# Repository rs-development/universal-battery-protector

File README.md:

# Work in Progress

# Universal Battery Protector
A Universal Battery Protector for Lithium Batteries with 2 to 6 Cells in series.

# LICENSE
<br />This work is licensed under a <a rel="license" href="http://creativecommons.org/licenses/by-sa/3.0/">Creative Commons Attribution-ShareAlike 3.0 Unported License</a>.

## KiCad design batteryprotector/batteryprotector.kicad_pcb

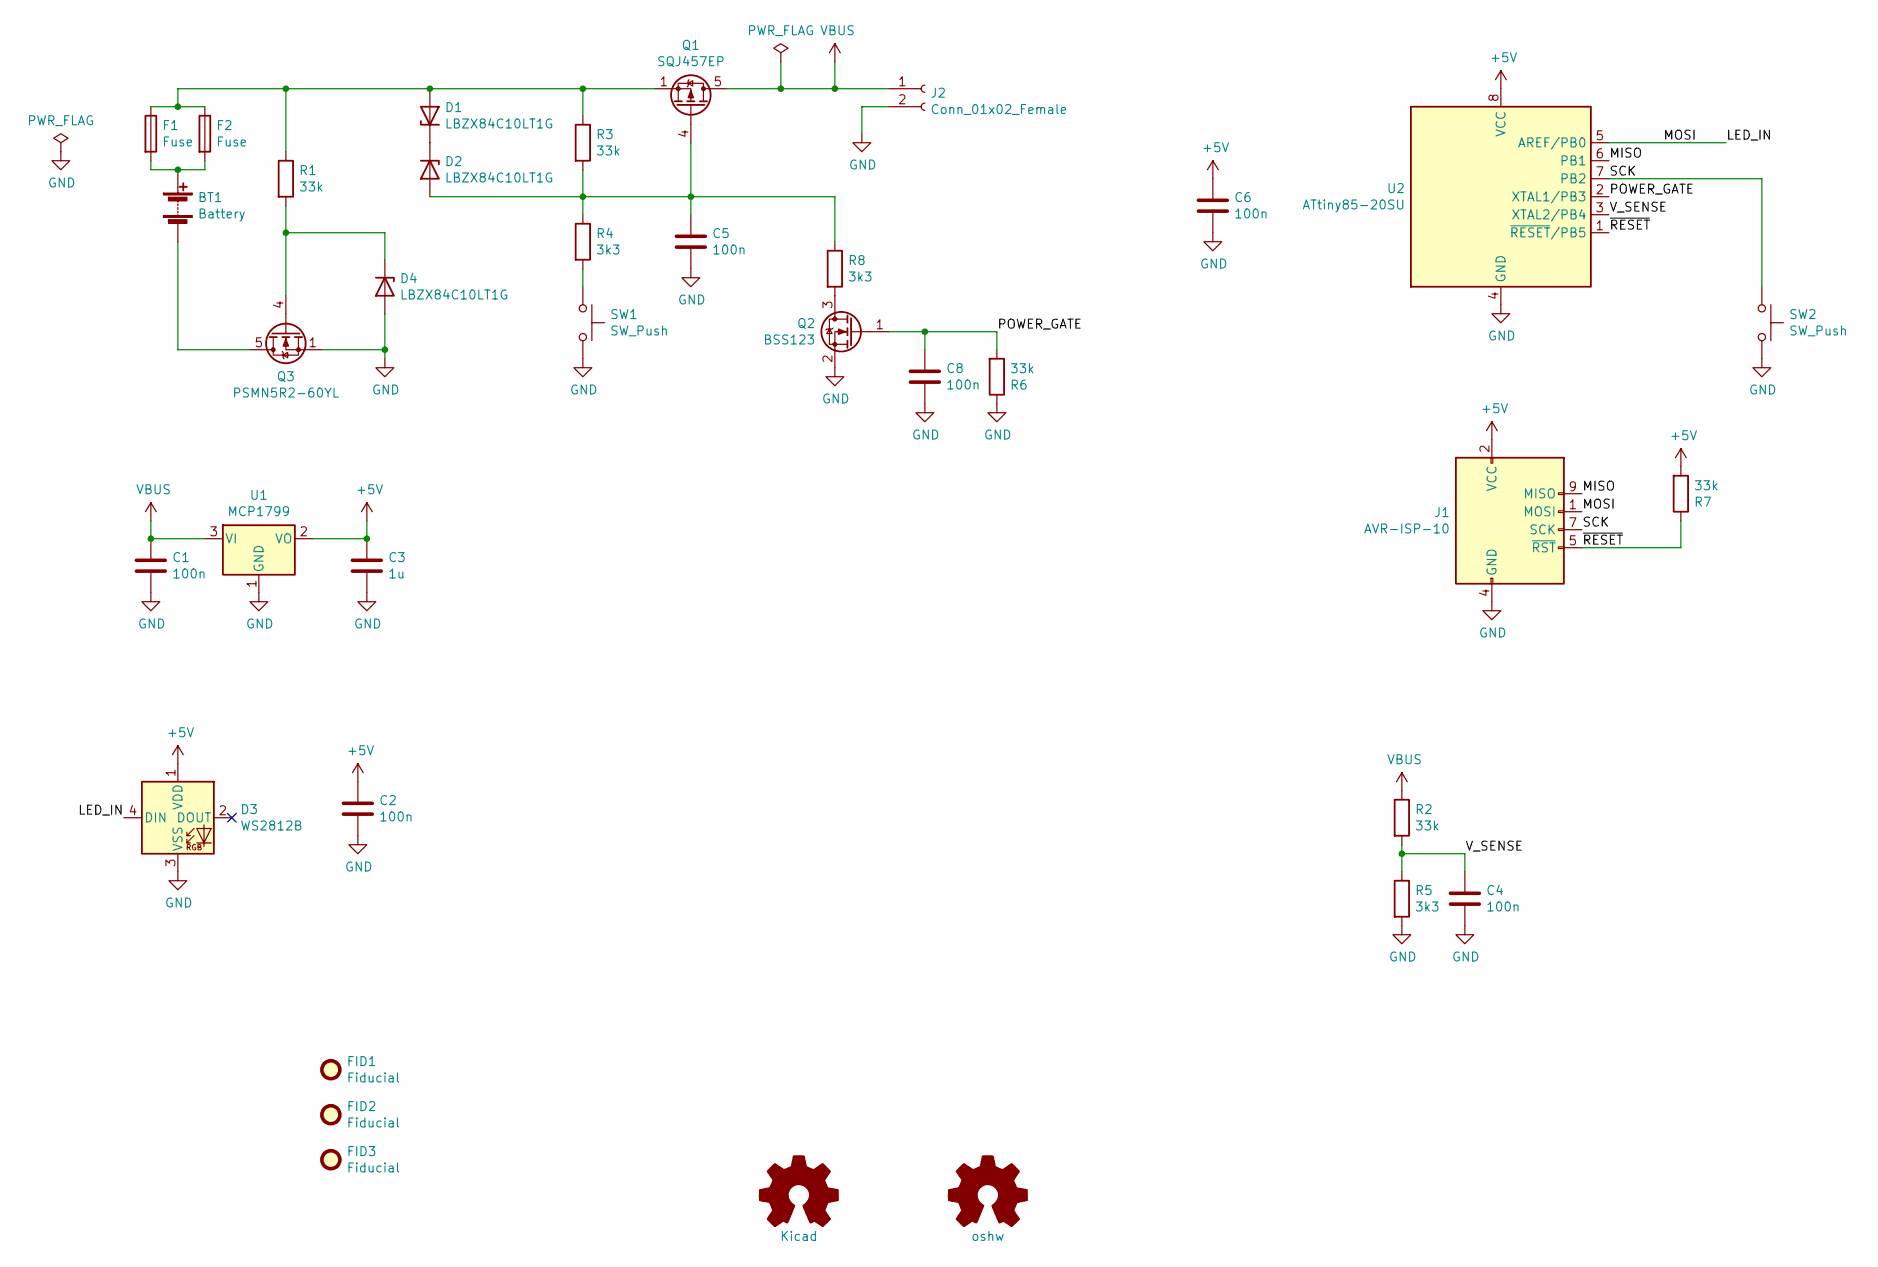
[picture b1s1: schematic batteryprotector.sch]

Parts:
BT1: Battery; AMASS_XT60-M_1x02_P7.20mm_Horizontal
C1, C2, C4, C5, C6, C8: 100n; C_0805_2012Metric
C3: 1u; C_0805_2012Metric
D1, D2, D4: LBZX84C10LT1G; D_SOT-23_ANK
D3: WS2812B; LED_WS2812B_PLCC4_5.0x5.0mm_P3.2mm
F1: Fuse; Fuse_1206_3216Metric
F2: Fuse; Fuse_0603_1608Metric
FID1, FID2, FID3: Fiducial; Fiducial_1mm_Mask2mm_Paste
J1: AVR-ISP-10; Tag-Connect_TC2050-IDC-NL_2x05_P1.27mm_Vertical
J2: Conn_01x02_Female; AMASS_XT60-F_1x02_P7.20mm_Horizontal
LOGO1: oshw; OSHW-Logo2_7.3x6mm_SilkScreen
LOGO2: Kicad; KiCad-Logo2_5mm_SilkScreen
Q1: SQJ457EP; LFPAK56
Q2: BSS123; SOT-23
Q3: PSMN5R2-60YL; LFPAK56
R1, R2, R3, R6, R7: 33k; R_0805_2012Metric
R4, R5, R8: 3k3; R_0805_2012Metric
SW1, SW2: SW_Push; SW_SPST_PTS810
U1: MCP1799; SOT-23
U2: ATtiny85-20SU; SOIJ-8_5.3x5.3mm_P1.27mm

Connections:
+5V: C2.1, C3.1, C6.1, D3.1 (VDD), J1.2 (VCC), R7.2, U1.2 (VO), U2.8 (VCC)
/LED_IN: D3.4 (DIN), J1.1 (MOSI), U2.5 (AREF/PB0)
/MISO: J1.9 (MISO), U2.6 (PB1)
/POWER_GATE: C8.1, Q2.1 (G), R6.2, U2.2 (XTAL1/PB3)
/SCK: J1.7 (SCK), SW2.1, U2.7 (PB2)
/V_SENSE: C4.1, R2.2, R5.1, U2.3 (XTAL2/PB4)
/~RESET: J1.5 (~RST), R7.1, U2.1 (~RESET~/PB5)
GND: C1.2, C2.2, C3.2, C4.2, C5.2, C6.2, C8.2, D3.3 (VSS), D4.2 (A), J1.4 (GND), J1.6 (GND), J1.8 (GND), J1.10 (GND), J2.2, Q2.2 (S), Q3.1 (S), Q3.2 (S), Q3.3 (S), R5.2, R6.1, SW1.2, SW2.2, U1.1 (GND), U2.4 (GND)
unnamed: BT1.1 (+), F1.2, F2.2
unnamed: BT1.2 (-), Q3.5 (D)
unnamed: C5.1, D2.2 (A), Q1.4 (G), R3.2, R4.1, R8.1
unnamed: D1.1 (K), D2.1 (K)
unnamed: D1.2 (A), F1.1, F2.1, Q1.1 (S), Q1.2 (S), Q1.3 (S), R1.1, R3.1
unnamed: D4.1 (K), Q3.4 (G), R1.2
unnamed: Q2.3 (D), R8.2
unnamed: R4.2, SW1.1
VBUS: C1.1, J2.1, Q1.5 (D), R2.1, U1.3 (VI)

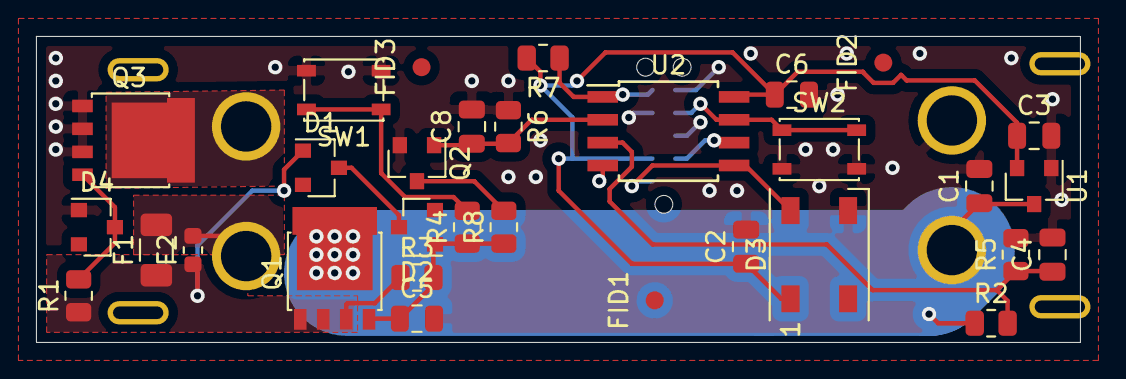
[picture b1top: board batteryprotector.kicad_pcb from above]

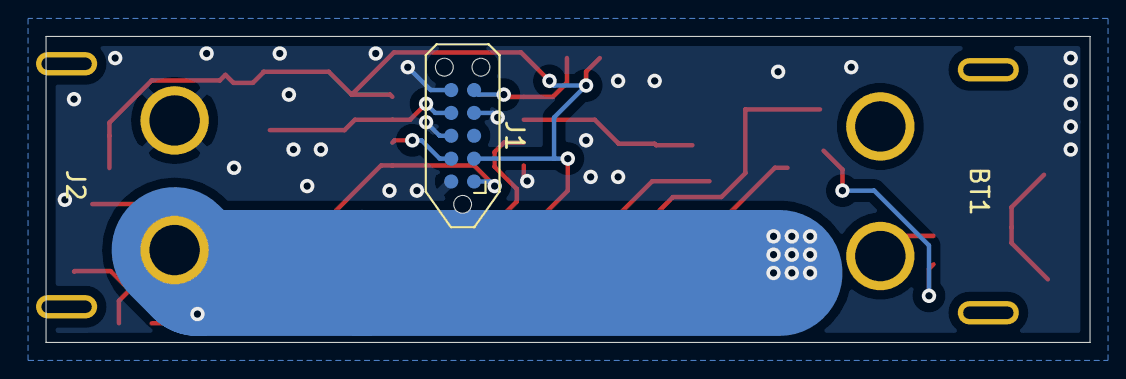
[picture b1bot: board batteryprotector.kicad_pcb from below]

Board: 2 copper layers, 58.0 x 17.0 mm, 36 parts (3 on the bottom side), 17 nets.

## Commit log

2021-04-05 initial
2021-04-05 layout start
2021-04-05 added license
2021-04-06 routing
